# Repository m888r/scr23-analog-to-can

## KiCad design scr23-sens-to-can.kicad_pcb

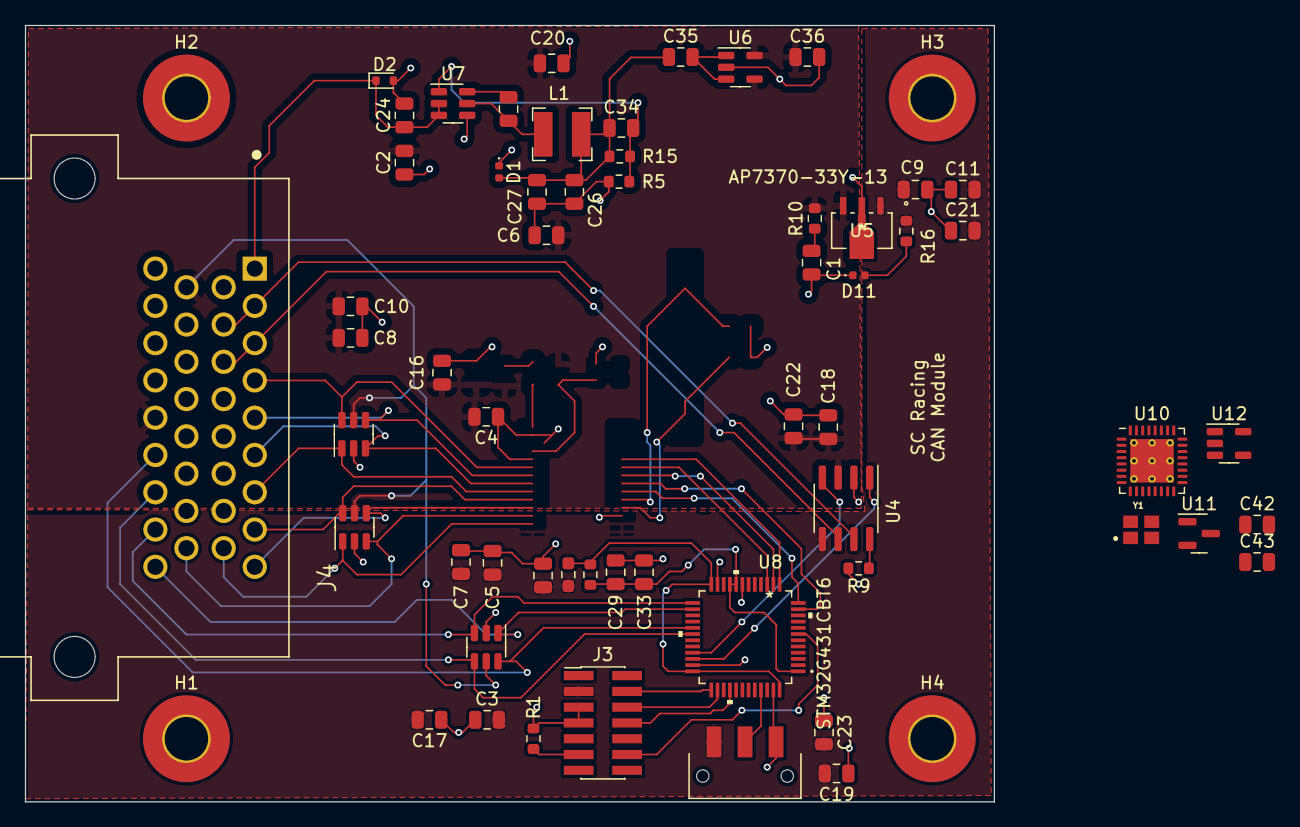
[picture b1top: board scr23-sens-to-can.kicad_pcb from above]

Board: 2 copper layers, 78.0 x 62.5 mm, 62 parts (0 on the bottom side), 46 nets.

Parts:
C1, C23, C24: 10uF; C_0805_2012Metric
C2, C3, C4, C5, C6, C7, C8, C9, C10, C11, C16, C17, C18, C19, C20, C21, C22, C25: 100nF; C_0805_2012Metric
C26, C27: 22uF; C_0805_2012Metric
C28: TCP0J106M8R; C_0805_2012Metric
C29: 1u; C_0805_2012Metric
C33: 100n; C_0805_2012Metric
C34: 100pF; C_0805_2012Metric
C35, C36: 2.2uF; C_0805_2012Metric
C42, C43: 1uF; C_0805_2012Metric
D1, D11: LED-GREEN; LED_0402_1005Metric
D2: D_TVS; D_SOD-523
FB1: 400; R_0603_1608Metric
H1, H2, H3, H4: Hole; MountingHole_3.5mm_Pad_TopBottom
J3: Conn_ST_STDC14; PinHeader_2x07_P1.27mm_Vertical_SMD
J4: 6437288-2; TE_6437288-2
L1: 10uH; L_Bourns-SRN4018
R1: 100; R_0603_1608Metric
R4: 0; R_0603_1608Metric_Pad0.98x0.95mm_HandSolder
R5: 34k; R_0603_1608Metric
R9: 100k; R_0603_1608Metric
R10, R16: 1k; R_0603_1608Metric
R15: 221k; R_0603_1608Metric
SW1: SW_SPDT; SW_JS102011SAQN
U1, U2, U9: SRV05-4; SOT-23-6
U4: TJA1042T-3; SOIC-8_3.9x4.9mm_P1.27mm
U5: AP7370-33Y-13
U6: ADP7142AUJZ-5.0; TSOT-23-5
U7: AP63200WU; TSOT-23-6
U8: STM32G431CBT6
U10: ADS8168IRHBT; VQFN-32-1EP_5x5mm_P0.5mm_EP3.5x3.5mm_ThermalVias
U11: LM4040DBZ-5; SOT-23
U12: OPA320AIDBVR; SOT-23-5
Y1: ECS-160-8-36B-CKY-TR3; XTAL_ECS-163.84-10-36-JGN-TR

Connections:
5V_REF: U10.3 (REFIO), U11.1 (K)
+3.3V: C3.2, C5.2, C7.2, C9.2, C11.2, C17.2, C19.2, C21.2, C23.2, C28.1, C42.2, J3.3 (VCC), R4.2, R16.1, SW1.1 (A), U4.5 (VIO), U5.1 (VOUT), U10.30 (DVDD)
+3.3VA: C29.1, C33.1, FB1.2, U8.1 (VBAT), U8.20 (VREF+), U8.21 (VDDA)
+5V: C2.2, C4.2, C6.2, C8.2, C10.2, C16.2, C18.2, C20.2, C22.2, C36.1, C43.2, J4.18, J4.30, R10.1, U1.5 (VP), U2.5 (VP), U4.3 (VCC), U5.3 (VIN), U6.4 (SENSE/ADJ), U6.5 (VOUT), U9.5 (VP), U10.32 (AVDD), U12.5 (V+)
+6V: C26.1, C27.1, C34.1, C35.1, D1.2 (A), L1.2, R15.1
+12V: C24.1, D2.1 (A1), J4.1, U7.2 (EN), U7.3 (IN)
/ADC_BUF_IN: U10.18 (MUXOUT-P), U12.3 (+)
/NRST: J3.12 (~RST), U8.7 (PG10-NRST)
/OSC_IN: U8.5 (PF0-OSC_IN), Y1.3 (OUT/IN)
/OSC_OUT: U8.6 (PF1-OSC_OUT), Y1.1 (IN/OUT)
A0: J4.4, U1.6 (IO4), U10.9 (AIN0)
A1: J4.5, U1.4 (IO3), U10.10 (AIN1)
A2: J4.6, U1.3 (IO2), U10.11 (AIN2)
A3: J4.7, U1.1 (IO1), U10.12 (AIN3)
A4: J4.8, U9.6 (IO4), U10.13 (AIN4)
A5: J4.9, U9.4 (IO3), U10.14 (AIN5)
A6: J4.25, U9.3 (IO2), U10.15 (AIN6)
A7: J4.17, U9.1 (IO1), U10.16 (AIN7)
ADC_CS: U8.12 (PA4), U10.23 (*CS)
ADC_SCLK: U8.13 (PA5), U10.25 (SCLK)
ADC_SDI: U8.15 (PA7), U10.24 (SDI)
ADC_SDO: U8.14 (PA6), U10.26 (SDO-0)
CANH: J4.2, J4.11, U4.7 (CANH)
CANL: J4.3, J4.12, U4.6 (CANL)
CAN_STB: R9.1, U4.8 (STB)
D0: J4.33, U2.3 (IO2), U8.25 (PB11)
D1: J4.34, U2.1 (IO1), U8.26 (PB12)
D2: J4.31, U2.6 (IO4), U8.29 (PB15)
D3: J4.32, U2.4 (IO3), U8.30 (PA8)
DATA_READY: U8.11 (PA3), U10.28 (READY)
FDCAN1_RX: U4.4 (RXD), U8.33 (PA11)
FDCAN1_TX: U4.1 (TXD), U8.34 (PA12)
GND: C1.2, C2.1, C3.1, C4.1, C5.1, C6.1, C7.1, C8.1, C9.1, C10.1, C11.1, C16.1, C17.1, C18.1, C19.1, C20.1, C21.1, C22.1, C23.1, C24.2, C26.2, C27.2, C28.2, C29.2, C33.2, C36.2, C42.1, C43.1, D1.1 (K), D2.2 (A2), D11.1 (K), H1.1, H2.1, H3.1, H4.1, J3.5 (GND), J3.7 (GND), J4.13, J4.14, J4.15, R1.1, R5.2, R9.2, SW1.3 (C), U1.2 (VN), U2.2 (VN), U4.2 (GND), U5.2 (GND), U6.2 (GND), U7.4 (GND), U8.19 (VSSA), U8.23 (VSS), U8.35 (VSS), U8.47 (VSS), U9.2 (VN), U10.1 (GND), U10.4 (REFM), U10.8 (AIN-COM), U10.21 (GND), U10.31 (GND), U10.33 (EPAD), U11.2 (A), U12.2 (V-), Y1.2 (GND), Y1.4 (GND)
unnamed: C1.1, R10.2
unnamed: U10.5 (REFP), U10.6 (REFP)
unnamed: D11.2 (A), R16.2
unnamed: FB1.1, R4.1, U8.24 (VDD), U8.36 (VDD), U8.48 (VDD)
unnamed: J3.11 (GNDDetect), R1.2
unnamed: SW1.2 (B), U8.45 (PB8-BOOT0)
unnamed: C35.2, U6.1 (VIN), U6.3 (EN)
unnamed: C25.2, U7.6 (BST)
unnamed: C34.2, R5.1, R15.2, U7.1 (FB)
unnamed: C25.1, L1.1, U7.5 (SW)
SWCLK: J3.6 (JCLK/SWCLK), U8.38 (PA14)
SWDIO: J3.4 (JTMS/SWDIO), U8.37 (PA13)
SWO: J3.8 (JTDO/SWO), U8.40 (PB3)

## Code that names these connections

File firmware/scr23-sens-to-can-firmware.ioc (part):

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Mcu.Name=STM32G431C(6-8-B)Tx
Mcu.Package=LQFP48
Mcu.UserName=STM32G431CBTx
PA11.Mode=FDCAN_Activate
PA11.Signal=FDCAN1_RX
PA12.Mode=FDCAN_Activate
PA12.Signal=FDCAN1_TX
PA13.Mode=Trace_Asynchronous_SW
PA13.Signal=SYS_JTMS-SWDIO
PA14.Mode=Trace_Asynchronous_SW
PA14.Signal=SYS_JTCK-SWCLK
PA4.Signal=GPIO_Output
PA5.Mode=Full_Duplex_Master
PA5.Signal=SPI1_SCK
PA6.Mode=Full_Duplex_Master
PA6.Signal=SPI1_MISO
PA7.Mode=Full_Duplex_Master
PA7.Signal=SPI1_MOSI
PA8.Signal=GPIO_Input
PB11.Signal=GPIO_Input
PB12.Signal=GPIO_Input
PB15.Signal=GPIO_Input
PB3.Mode=Trace_Asynchronous_SW
PB3.Signal=SYS_JTDO-SWO
PB4.Mode=Dual_Role_AllSignals
PB4.Signal=UCPD1_CC2
PB6.Mode=Dual_Role_AllSignals
PB6.Signal=UCPD1_CC1
RCC.HSE_VALUE=8000000
RCC.SYSCLKFreq_VALUE=16000000
board=custom

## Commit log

2022-10-17 add TODOs and stuff
2022-10-18 update pinouts, update uC and add comments/segmentation
2022-10-18 add CAN, start 3.3va circuit
2022-10-18 idk why so many changes happened but I replaced the 5v LDO with a massive one
2022-10-18 pick stm32 adc pins and section out decoupling cap + input buffer area
2022-10-18 change block title
2022-10-18 add old backup
2022-10-20 add buffer circuit using lm358QT (dfn8x8) tho it's out of stock on lcsc in stock digikey
2022-10-20 add hella caps and fix odds and ends + numbering
2022-10-25 added boot0 spdt
2022-10-25 change decoupling caps
2022-10-27 change caps on 5v reg and put 5v/3.3v regulators in series
2022-10-28 switch to smps, add uC power supply filtering
2022-10-28 add notes
2022-11-18 add tantalum decoupling cap to stm32 power rail
2022-11-26 spec smps inductor, might want to go 6.8uH with ~2.5A according to equations...but went 2A 4.7uH :)
2023-02-09 add footprints
2023-02-16 capacitors
2023-03-02 final footprints
2023-03-03 begin layout
2023-03-11 layout & traces in progress
2023-03-11 layout progress
2023-03-13 rotate tranceiver
2023-05-24 change connectors
2023-05-24 add external ADC, not pinned yet
2023-05-25 switch to external ADC, switch to amp superseal 1.0 for connector, need to check CANFD pins disagreement with datasheet
2023-05-25 slight schematic changes, refer to last commit message
2023-05-25 add another TVS array for digital input/outputs
2023-05-26 really close to being done with schematic, need to verify stuff for ADC with page 28 of ADC datasheet
2023-05-26 one missed save, also definitely need to change vref+
2023-05-26 add voltage reference, might need to change switching regulator cap packages
2023-05-28 add tantalum 10u cap and 0R resistor to tune ferrite bead filter
2023-05-28 add vref+ wiring to stm32g4
2023-06-17 switch voltage regulation scheme
2023-08-24 added some comments for WIP stuff
2023-09-26 added 34 pin connector, gonna add two CAN transceivers and switch to g474
2023-10-17 change switching regulator
2023-10-18 finish layout mk1
2023-10-24 add LDO
2023-10-26 add ADS8167IRHBT, higher bit + higher sampling rate ADC, another option is ADS8668 since that's 12v tolerant, idk
2023-10-26 component
2023-11-13 finish traces for new connector
2024-01-26 add ads8168, need to add mux op amp, switch 5v LDO to a more common one possibly, and maybe a bunch of 0R resistors and empty capacitor footprints in case we wanna add low pass filters
2024-01-26 add datasheet link to ads8168
2024-02-02 ads8168 adc schematic finished
2024-02-09 add uC crystal, finish swap to ads8168, need to add some footprints to passives and redo layout
2024-02-27 updated to kicad 8.0
2024-02-27 update pcb layout not done

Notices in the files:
parts and their libraries:
Copyright 2021 Accelerated Designs. All rights reserved.
